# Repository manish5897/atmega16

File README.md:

# atmega16
Atmega16 Schematic and Layout

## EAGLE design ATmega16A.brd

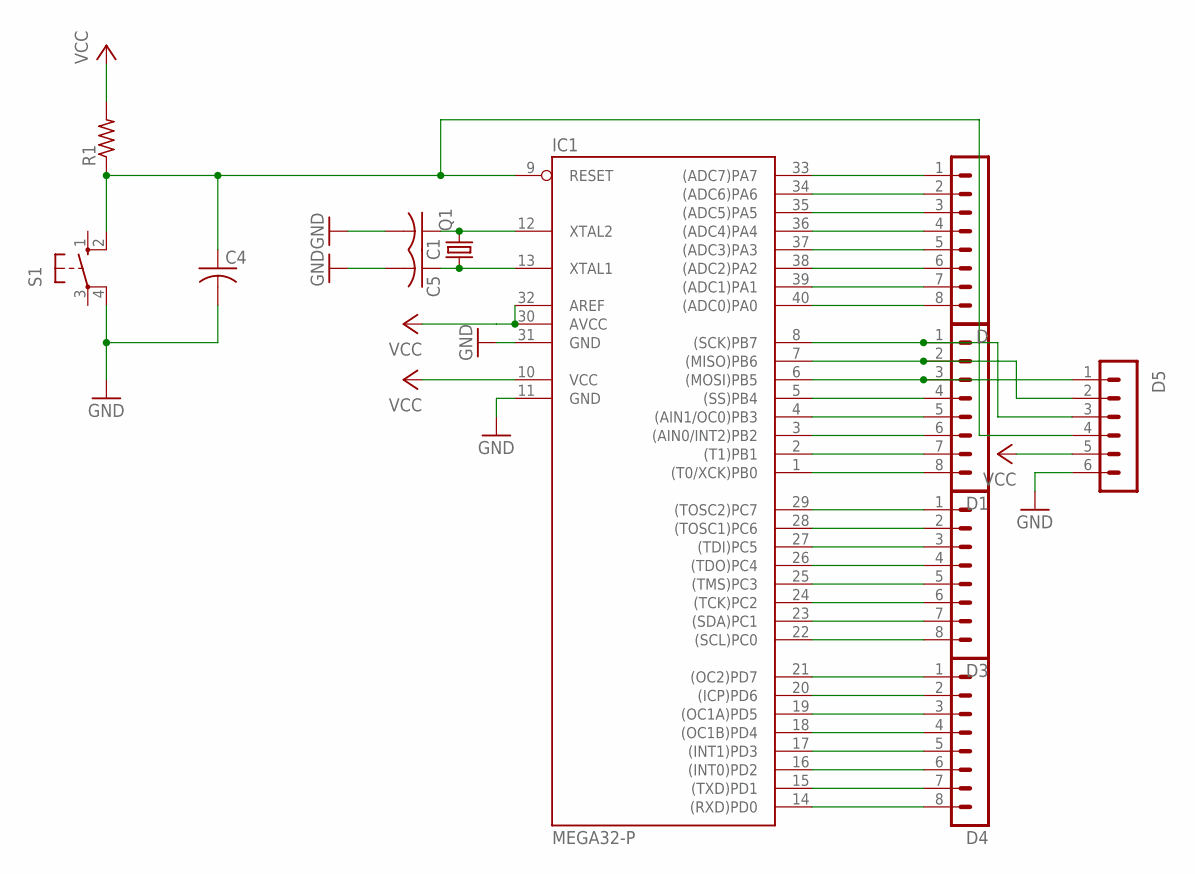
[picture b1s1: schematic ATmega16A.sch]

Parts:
C1, C4, C5: C-US025-025X050; C025-025X050
D, D1, D3, D4: MA08-1
D5: MA06-1
IC1: MEGA32-P; DIL40
Q1: CRYSTALHC49S; HC49/S
R1: R-US_0204/7; 0204/7
S1: 10-XX; B3F-10XX

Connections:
GND: C1.2, C4.2, C5.2, D5.6, IC1.11 (GND), IC1.31 (GND), S1.4 (P1)
unnamed: D.1, IC1.33 ((ADC7)PA7)
unnamed: D.2, IC1.34 ((ADC6)PA6)
unnamed: D.3, IC1.35 ((ADC5)PA5)
unnamed: D.4, IC1.36 ((ADC4)PA4)
unnamed: D.5, IC1.37 ((ADC3)PA3)
unnamed: D.6, IC1.38 ((ADC2)PA2)
unnamed: D.7, IC1.39 ((ADC1)PA1)
unnamed: D.8, IC1.40 ((ADC0)PA0)
unnamed: D1.1, D5.3, IC1.8 ((SCK)PB7)
unnamed: D1.2, D5.2, IC1.7 ((MISO)PB6)
unnamed: D1.3, D5.1, IC1.6 ((MOSI)PB5)
unnamed: D1.4, IC1.5 ((SS)PB4)
unnamed: D1.5, IC1.4 ((AIN1/OC0)PB3)
unnamed: D1.6, IC1.3 ((AIN0/INT2)PB2)
unnamed: D1.7, IC1.2 ((T1)PB1)
unnamed: D1.8, IC1.1 ((T0/XCK)PB0)
unnamed: D3.1, IC1.29 ((TOSC2)PC7)
unnamed: D3.2, IC1.28 ((TOSC1)PC6)
unnamed: D3.3, IC1.27 ((TDI)PC5)
unnamed: D3.4, IC1.26 ((TDO)PC4)
unnamed: D3.5, IC1.25 ((TMS)PC3)
unnamed: D3.6, IC1.24 ((TCK)PC2)
unnamed: D3.7, IC1.23 ((SDA)PC1)
unnamed: D3.8, IC1.22 ((SCL)PC0)
unnamed: D4.1, IC1.21 ((OC2)PD7)
unnamed: D4.2, IC1.20 ((ICP)PD6)
unnamed: D4.3, IC1.19 ((OC1A)PD5)
unnamed: D4.4, IC1.18 ((OC1B)PD4)
unnamed: D4.5, IC1.17 ((INT1)PD3)
unnamed: D4.6, IC1.16 ((INT0)PD2)
unnamed: D4.7, IC1.15 ((TXD)PD1)
unnamed: D4.8, IC1.14 ((RXD)PD0)
unnamed: C1.1, IC1.12 (XTAL2), Q1.2
unnamed: C5.1, IC1.13 (XTAL1), Q1.1
unnamed: C4.1, D5.4, IC1.9 (RESET), R1.1, S1.2 (S1)
VCC: D5.5, IC1.10 (VCC), IC1.30 (AVCC), IC1.32 (AREF), R1.2

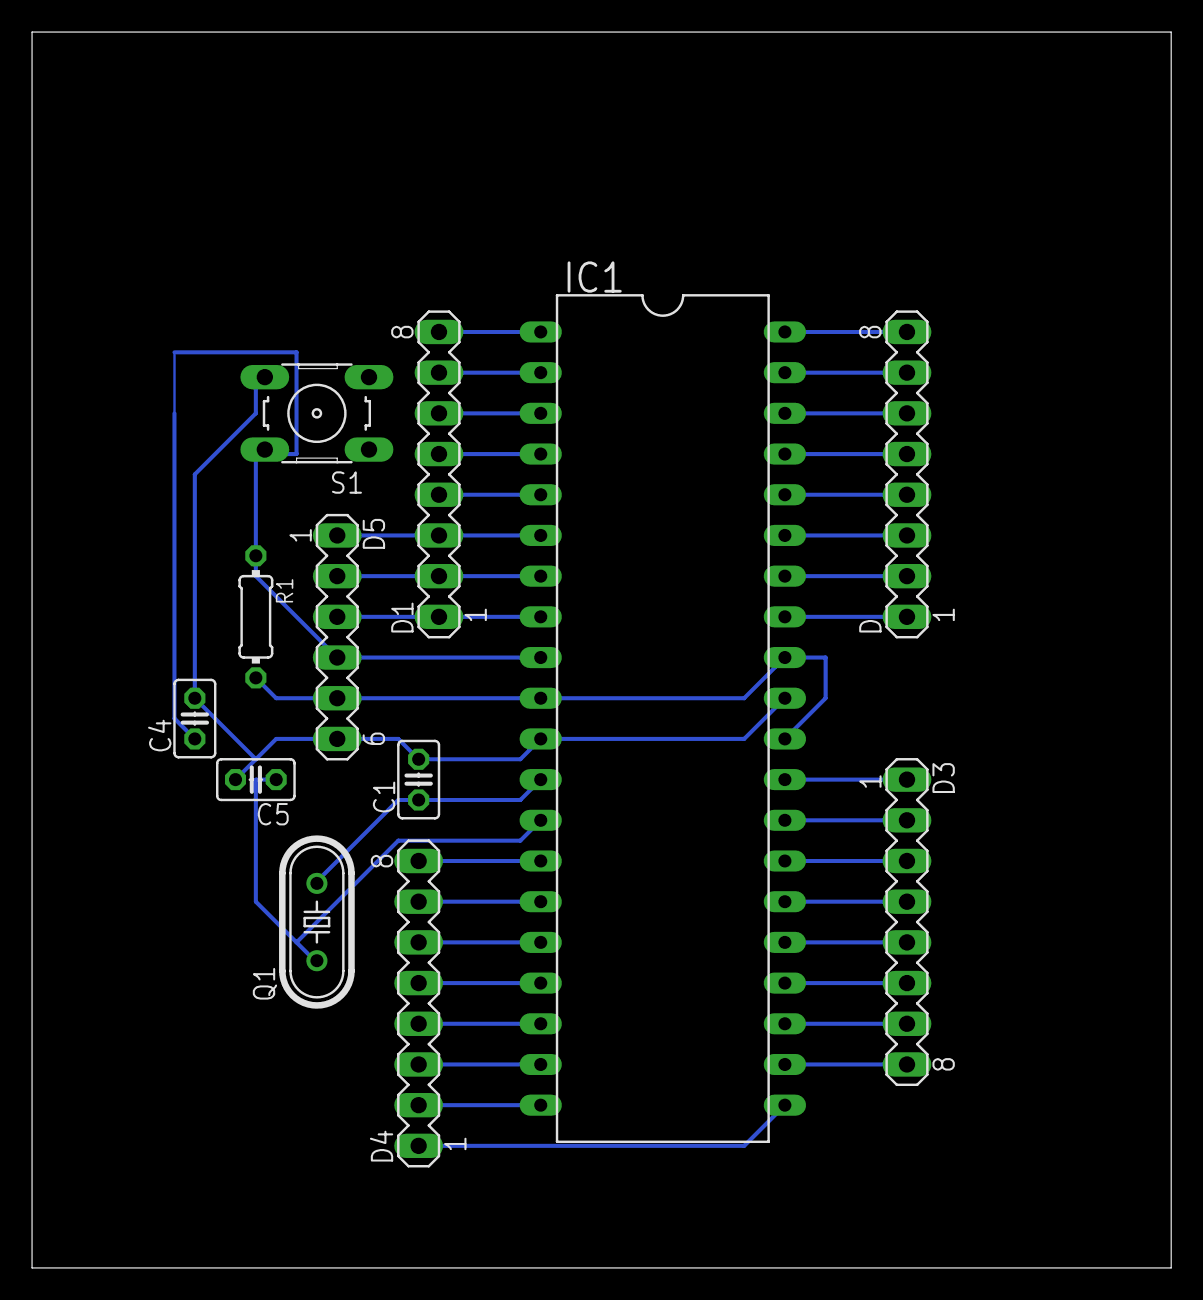
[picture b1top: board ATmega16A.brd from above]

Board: 2 copper layers, 71.1 x 77.1 mm, 12 parts (0 on the bottom side), 37 nets.

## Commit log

2018-08-12 atmega16 .sch and .brd file
